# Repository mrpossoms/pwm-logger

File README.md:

# PWM Logger / Generator

## Overview

The Protean PWM logger was designed to facilitate the development of hobbyist autonomous vehicle systems whose performance strongly depends on servo data collection and reproduction. The logger has the following default functions, but is fully reprogrammable.

* PWM signal generation for up to 6 channels.
* PMW signal decoding for up to 6 channels.
* Data access over I2C.

The PWM logger is built around Parallax's Propeller (P8X32A-Q44), an 8 core MCU which operates at ~20 MIPS per core. Dedicating each core's processing power to each servo channel offloads a potentially significant burden from your project's main computer. And allows for accurate decoding and generation of PWM signals.

## Usage

The PWM logger uses the I2C protocol for configuration and operation. It joins the bus as a slave device with the default 7-bit **address 0x69**. The logger is capable of, and tested with clock speeds of 100KHz and 400KHz but should be capable of higher speeds.

### Register usage

When configuring or using the PWM logger the first thing that your application will have to do is begin with an I2C write addressing the device and writing one byte which will select that register specifically. If you are planning on writing to the selected register you should continue with the current write transaction. Otherwise, end the transaction and follow up with a read.

### Device Registers

* 0x00 - Configuration register: Controls the mode of operation of the PWM logger. By default, the value in that register can have the following values.
   * 0 -> Echo off, this means the PWM logger will ignore PWM signals on the input channels. Instead it will generate the pulse width in the channel register.
   * 1 -> Echo on, this means the PWM logger will measure PWM signals on the input channels, and store the measurement in each channel register.
* 0x0N - Channel register: These registers store the pulse width as a pseudo time from [0, 255]. The pulse duration in seconds for a given channel register value can be obtained with the following operation (_value_ << 10) / _clock speed_ where the clock speed in the normal case is 8 * 10^7 Hz.
  * Once a channel register has been selected with a write, you can continue reading or writing multiple bytes as the selected register will be auto incremented. This allows you to collect data from, or write new timings to, all the servo channels in a single I2C transaction.
  * When the device is in echo mode the measured pulse widths are stored in each respective channel register.
  * When the device has echo mode disabled, the last pulse width in each channel register will be generated on that corresponding channel. That means writing to that register will cause the device to generate that particular pulse width.
* 0x0A - Firmware revision register: This register contains a single byte indicating the revision of the currently flashed firmware.
* 0x0B - Hardware reset register: Writing any value to this register will trigger a hardware reset of the board.

## Firmware

The PWM logger's firmware is written in PASM, the propeller's native language. More information about PASM can be found in the [propeller manual](https://www.parallax.com/sites/default/files/downloads/P8X32A-Web-PropellerManual-v1.2.pdf).

### Building & Flashing

For all platforms you will need to have Parallax's [SimpleIDE](http://learn.parallax.com/tutorials/language/propeller-c/propeller-c-set-simpleide) installed. It provides the necessary toolchain for assembling the source and flashing it to the propeller chip. You will also need a [Prop Plug](https://www.parallax.com/product/32201) to perform the actual flashing.

#### Mac / Linux

Once you have installed the SimpleIDE you will need to add the toolchain to your `PATH` environment variable. 

On MacOS the toolchain is likely to be found in `/Applications`. In my case, I was able to add it to my path like so.

```
export PATH="$PATH:/Applications/SimpleIDE.app/Contents/propeller-gcc/bin"
```

On linux, run the following command.

```
...
```

In both cases, you can make the change permanent by adding it to your `.bashrc` file (if bash is your shell).

After that, you should be ready to assemble the program and flash the board by using the following.

```
make flash
```

This will both assemble the program and flash the device. The program will run immediately. __Note:__ You may need to change the device file /dev/ttyUSB0 used in the Makefile to match the device file assigned to the Prop Plug on your system.

#### Windows

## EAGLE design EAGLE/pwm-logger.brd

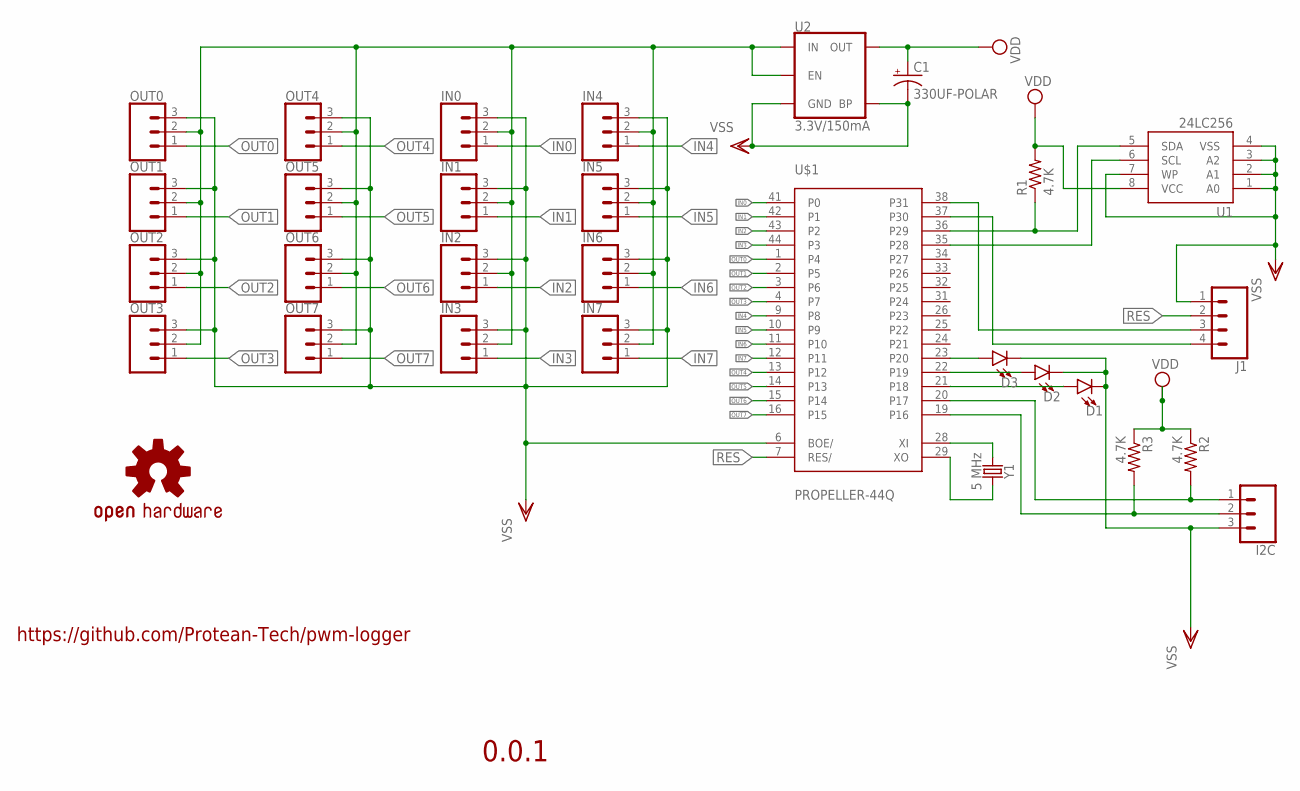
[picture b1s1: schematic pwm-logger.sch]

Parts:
C1: 330UF-POLAR; 1311
D1, D2, D3: LED-FKIT-1206; FKIT-LED-1206
I2C: CONN_03; 1X03
IN0, IN1, IN2, IN3, IN4, IN5, IN6, IN7: CONN_03; 1X03
J1: CONN_04; 1X04
LOGO1: OSHW-LOGOM; OSHW-LOGO-M
OUT0, OUT1, OUT2, OUT3, OUT4, OUT5, OUT6, OUT7: CONN_03; 1X03
R1, R2, R3: 4.7K; M2012
U1: 24LC256; SO08
U2: 3.3V/150mA; SOT23-5
U$1: PROPELLER-44Q; Q44
Y1: 5 MHz; HC49U

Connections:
IN0: IN0.1, U$1.41 (P0)
IN1: IN1.1, U$1.42 (P1)
IN2: IN2.1, U$1.43 (P2)
IN3: IN3.1, U$1.44 (P3)
IN4: IN4.1, U$1.9 (P8)
IN5: IN5.1, U$1.10 (P9)
IN6: IN6.1, U$1.11 (P10)
IN7: IN7.1, U$1.12 (P11)
unnamed: U$1.28 (XI), Y1.1
unnamed: U$1.29 (XO), Y1.2
unnamed: D3.A, U$1.23 (P20)
unnamed: D2.A, U$1.22 (P19)
unnamed: J1.3, U$1.38 (P31)
unnamed: D1.A, U$1.21 (P18)
unnamed: J1.4, U$1.37 (P30)
OUT0: OUT0.1, U$1.1 (P4)
OUT1: OUT1.1, U$1.2 (P5)
OUT2: OUT2.1, U$1.3 (P6)
OUT3: OUT3.1, U$1.4 (P7)
OUT4: OUT4.1, U$1.13 (P12)
OUT5: OUT5.1, U$1.14 (P13)
OUT6: OUT6.1, U$1.15 (P14)
OUT7: OUT7.1, U$1.16 (P15)
POWER_IN: IN0.2, IN1.2, IN2.2, IN3.2, IN4.2, IN5.2, IN6.2, IN7.2, OUT0.2, OUT1.2, OUT2.2, OUT3.2, OUT4.2, OUT5.2, OUT6.2, OUT7.2, U2.1 (IN), U2.3 (EN)
RES: J1.2, U$1.7 (RES/)
SCL: I2C.1, R2.2, U$1.20 (P17)
SCL_EEP: U1.6 (SCL), U$1.35 (P28)
SDA: I2C.2, R3.2, U$1.19 (P16)
SDA_EEP: R1.1, U1.5 (SDA), U$1.36 (P29)
VDD: C1.+, R1.2, R2.1, R3.1, U1.8 (VCC), U2.5 (OUT), U$1.8 (VDD), U$1.18 (VDD), U$1.30 (VDD), U$1.40 (VDD)
VSS: C1.-, D1.C, D2.C, D3.C, I2C.3, IN0.3, IN1.3, IN2.3, IN3.3, IN4.3, IN5.3, IN6.3, IN7.3, J1.1, OUT0.3, OUT1.3, OUT2.3, OUT3.3, OUT4.3, OUT5.3, OUT6.3, OUT7.3, U1.1 (A0), U1.2 (A1), U1.3 (A2), U1.4 (VSS), U1.7 (WP), U2.2 (GND), U2.4 (BP), U$1.5 (VSS), U$1.6 (BOE/), U$1.17 (VSS), U$1.27 (VSS), U$1.39 (VSS)

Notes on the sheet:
0.0.1
https://github.com/Protean-Tech/pwm-logger

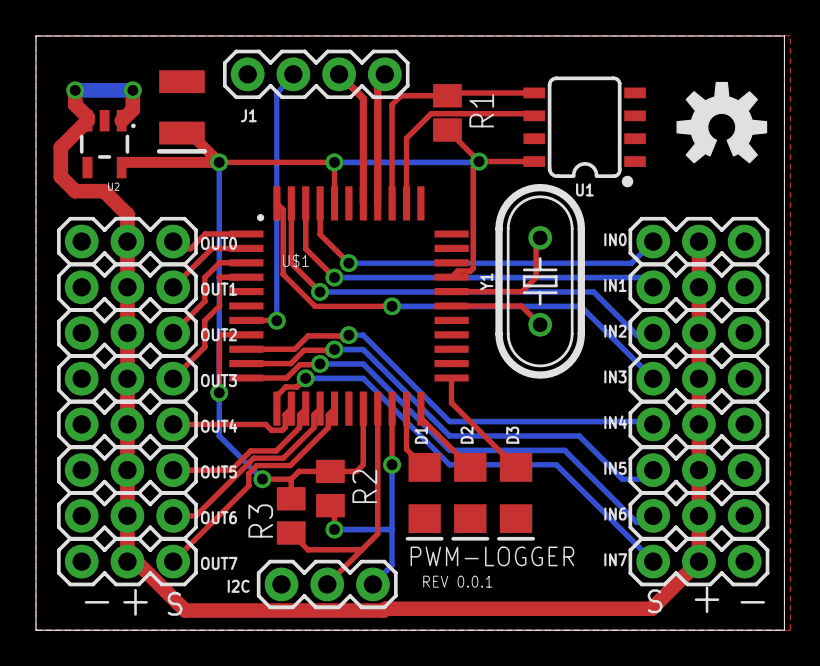
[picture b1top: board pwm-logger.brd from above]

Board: 2 copper layers, 41.6 x 33.0 mm, 30 parts (0 on the bottom side), 31 nets.

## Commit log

2017-06-12 Early source, measuring pulse widths
2017-06-13 Works if executed from cog0. Heading down the cogc path
2017-06-14 Moving to simple ide in hopes of resolving non-starting cogc modules
2017-06-14 Missed files
2017-06-19 Working on PASM firmware
2017-06-20 Working on i2c periph
2017-06-22 Working on i2c
2017-06-23 Better makefile rules
2017-06-23 Simplified i2c code a bit
2017-06-23 Device addressing working
2017-06-27 Working on detecting stop condition
2017-06-30 Got I2C line conditions working correctly :D
2017-06-30 Generic read and write are working :)
2017-06-30 Added register selection via the first byte read
2017-07-01 Echo is weird for some reason, but pwm generation seems initally stable
2017-07-03 Reading and writing the servo angle value over I2C is working :D
2017-07-03 Multiple servos on multiple cogs working
2017-07-03 Cleaned up asm formatting
2017-07-08 Some code documentation
2017-07-10 Register description and usage
2017-07-10 Added schematics and design files
2017-07-18 Added GNU GPL v3 license
2017-07-21 Added build.bat for windows
2017-07-21 Updated schematics
2017-08-01 Restructured the pwm-cog code a bit. Added version and reboot i2c registers
2017-08-01 Fixed I2C issues for board rev 0.0.1
2017-08-08 Fixed channel block bug. Fixed addesssing for channels
2017-08-08 Shifted active channels to 0 - 5 for release
2017-08-25 Added rotary encoder counter
2017-08-25 Missed encoder cog code
2017-09-02 Got rotory encoder functionality working
2017-09-10 Wheel encoder working
2017-09-29 Added ability to control echo on a per channel basis
2017-09-29 Channel independent echo working
2018-08-24 Added measurement of receiver values even when echo mode is off
2018-08-31 Added soft reset for odo. Renamed some pointer variables

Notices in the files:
parts and their libraries:
SparkFun-Connectors: Licensing: Creative Commons ShareAlike 4.0 International - https://creativecommons.org/licenses/by-sa/4.0
